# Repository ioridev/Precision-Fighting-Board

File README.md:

# [Precision-Fighting-Board](https://github.com/ioridev/Precision-Fighting-Board)

We all need to use this board in 20XX.  
[Discussions](https://github.com/ioridev/Precision-Fighting-Board/discussions)  
## Description

This project aims to develop the fastest game controller by utilizing the power of [Teensy 4.0](https://www.pjrc.com/store/teensy40.html). We strive to achieve a polling rate of 8000Hz, delivering unparalleled responsiveness for an immersive gaming experience.

## Where to Buy
  
Available for purchase on Booth. Buying from this shop directly supports the developers. For international customers, shipping outside of Japan is possible using address forwarding services like Buyee and Tenso.  

[https://iori-giken.booth.pm/](https://iori-giken.booth.pm/)

## Features

- High-speed USB communication using [Teensy 4.0](https://www.pjrc.com/store/teensy40.html)
- Targeting an impressive 8000Hz polling rate
- Precise and instantaneous input response
- X-input support
- No waiting time for debounce

## Installation
Open the PrecisionFightingBoard.TEENSY40.hex file in [Teensyduino 1.53](https://www.pjrc.com/teensy/td_158/TeensyduinoInstall.exe) and write to [Teensy 4.0](https://www.pjrc.com/store/teensy40.html).　
| Pin Number | Button      |
|------------|-------------|
| 0          | Up       |
| 1          | Down   |
| 2          | Left      |
| 3          | Right    |
| 4          | Home   |
| 5          | Back     |
| 6          | Start     |
| 7          | Y           |
| 8          | X           |
| 9          | RB         |
| 10         | LB         |
| 11         | A            |
| 12         | B            |
| 14         | RT         |
| 15         | LT          |
| 18         | L3          |
| 19         | R3          |

### Tips
Not good at soldering or making wires?  
Some models are equipped with pins from the beginning, so you can skip this complicated process by using this type of wire and wire for Brook.  
[Teensy 4.0 Pins](https://www.pjrc.com/store/teensy40_pins.html)

One GND with a pin is missing, so it must be branched with a breadboard or similar.　 

Or you can purchase Breakout Board on Amazon.  
  
[Breakout Board for Teensy 4.0](https://www.amazon.com/dp/B0C5SXFTC1?_encoding=UTF8&psc=1&ref_=cm_sw_r_cp_ud_dp_3P4ZTVVE18NE8B7TW8SG)

## Setting Up the Development Environment
Install Arduino IDE 1.8.13 and Teensyduino 1.53.

Clone this repository and copy the x-input/ArduinoXinput_Teensy/teensy directory to C:\Program Files (x86)\Arduino\hardware.

Open PrecisionFightingBoard.ino with the Arduino IDE, go to Tools, change the USB Type to XInput, and then upload it to the Teensy 4.0.

## Benchmark
### Polling rate test results 
I caught the continuous X-input button loop in my Python program and confirmed that it was around 0.125 ms.  
  
The program used for the test is in Precision-Fighting-Board/x-input/tester and anyone can try it out.

### Comparison with PicoBoard
tester/gamepad_response_time_comparison.py  
Gamepad 1 is a Precision-Fighting-Board.  
Gamepad 2 is a gp2040-ce  

### Comparison with Brook PS4+ Audio Fighting Board
Gamepad 1 is a Precision-Fighting-Board.  
Gamepad 2 is a Brook AFB  

### Use with WingmanFGC　
This is a test on a PC, but when used with WingmanFGC.  
Gamepad 1 is a Precision-Fighting-Board with WingmanFGC.  
Gamepad 2 is a gp2040-ce  
  
Good results with input lag of up to 5 ms.　　　

## Contributing

Contributions are welcome! If you'd like to contribute to this project, please follow these steps:

1. Fork the repository.
2. Create a new branch.
3. Make your enhancements or bug fixes.
4. Test thoroughly.
5. Submit a pull request detailing your changes.

## License

This project is licensed under the [MIT License](https://opensource.org/licenses/MIT). Please see the `LICENSE` file for more information.

## Acknowledgements

We would like to express our gratitude to the developers and contributors of Teency 4.0 for their amazing work and support.

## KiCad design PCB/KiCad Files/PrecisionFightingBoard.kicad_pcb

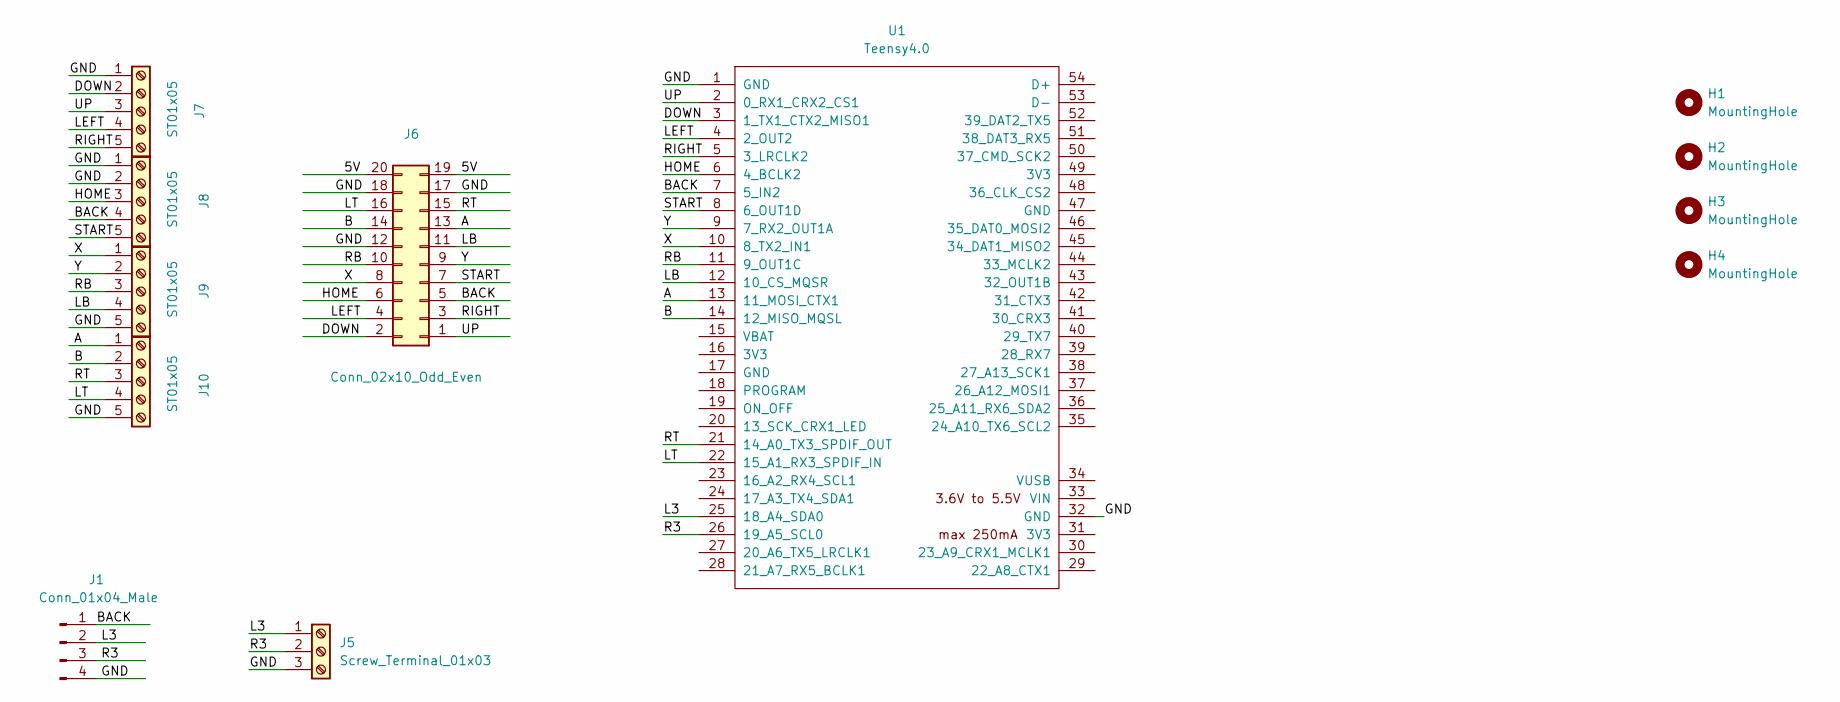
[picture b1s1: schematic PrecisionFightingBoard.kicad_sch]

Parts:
H1, H2, H3, H4: MountingHole; MountingHole_3.5mm
J1: Conn_01x04_Male; JST_PH_B4B-PH-K_1x04_P2.00mm_Vertical
J5: Screw_Terminal_01x03; TerminalBlock_MetzConnect_Type059_RT06303HBWC_1x03_P3.50mm_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
J6: Conn_02x10_Odd_Even; PinHeader_2x10_P2.54mm_Vertical
J7, J8, J9, J10: ST01x05; TerminalBlock_MetzConnect_Type059_RT06305HBWC_1x05_P3.50mm_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
U1: Teensy4.0; Teensy40

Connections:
/5V: J6.19, J6.20
/A: J6.13, J10.1, U1.13 (11_MOSI_CTX1)
/B: J6.14, J10.2, U1.14 (12_MISO_MQSL)
/BACK: J1.1, J6.5, J8.4, U1.7 (5_IN2)
/DOWN: J6.2, J7.2, U1.3 (1_TX1_CTX2_MISO1)
/GND: J1.4, J5.3, J6.12, J6.17, J6.18, J7.1, J8.1, J8.2, J9.5, J10.5, U1.1 (GND), U1.32 (GND)
/HOME: J6.6, J8.3, U1.6 (4_BCLK2)
/L3: J1.2, J5.1, U1.25 (18_A4_SDA0)
/LB: J6.11, J9.4, U1.12 (10_CS_MQSR)
/LEFT: J6.4, J7.4, U1.4 (2_OUT2)
/LT: J6.16, J10.4, U1.22 (15_A1_RX3_SPDIF_IN)
/R3: J1.3, J5.2, U1.26 (19_A5_SCL0)
/RB: J6.10, J9.3, U1.11 (9_OUT1C)
/RIGHT: J6.3, J7.5, U1.5 (3_LRCLK2)
/RT: J6.15, J10.3, U1.21 (14_A0_TX3_SPDIF_OUT)
/START: J6.7, J8.5, U1.8 (6_OUT1D)
/UP: J6.1, J7.3, U1.2 (0_RX1_CRX2_CS1)
/X: J6.8, J9.1, U1.10 (8_TX2_IN1)
/Y: J6.9, J9.2, U1.9 (7_RX2_OUT1A)

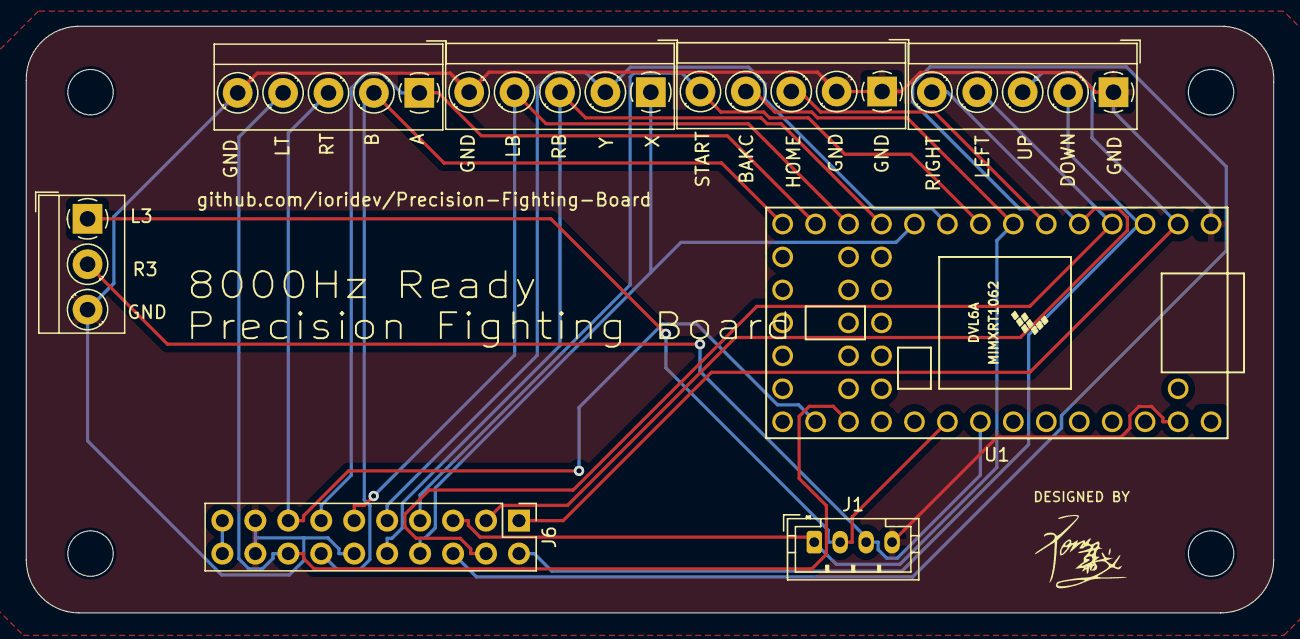
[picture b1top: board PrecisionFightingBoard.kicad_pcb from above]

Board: 2 copper layers, 96.1 x 45.2 mm, 12 parts (0 on the bottom side), 19 nets.

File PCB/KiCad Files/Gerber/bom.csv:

Designator,Footprint,Quantity,Value,LCSC Part #
"H1, H2, H3, H4",MountingHole_3.5mm,4,MountingHole,
J1,JST_PH_B4B-PH-K_1x04_P2.00mm_Vertical,1,Conn_01x04_Male,
"J10, J7, J8, J9",TerminalBlock_MetzConnect_Type059_RT06305HBWC_1x05_P3.50mm_Horizontal,4,ST01x05,
J5,TerminalBlock_MetzConnect_Type059_RT06303HBWC_1x03_P3.50mm_Horizontal,1,Screw_Terminal_01x03,
J6,PinHeader_2x10_P2.54mm_Vertical,1,Conn_02x10_Odd_Even,
U1,Teensy40,1,Teensy4.0,

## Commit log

2023-07-02 init
2023-07-02 add xinput
2023-07-02 add buttons
2023-07-02 rm: d-input
2023-07-02 add testar
2023-07-02 Create LICENSE
2023-07-02 fix d-input test program
2023-07-03 add d-input
2023-07-03 keyboard
2023-07-03 fix testar
2023-07-03 fix using pin
2023-07-03 add ArduinoXInput_Teensy
2023-07-03 rm teescy 3
2023-07-03 fix tester
2023-07-03 fix pin
2023-07-03 set xinput 8000Hz
2023-07-03 set 8000hz
2023-07-03 Make button pins easy to recognize.
2023-07-03 socd
2023-07-03 add license
2023-07-04 Update handle button bounce
2023-07-04 fix pit number
2023-07-04 add hex file
2023-07-04 Use eager debounce algorithm
2023-07-05 update hex file
2023-07-05 Improve debouncing in PrecisionFightingBoard.ino
2023-07-05 Refactor PrecisionFightingBoard.TEENSY40.hex for improved performance
2023-07-05 Improve debounce interval on PrecisionFightingBoard
2023-07-05 Refactor comments and improve explanation of debouncing behavior
2023-07-05 Optimize code for PrecisionFightingBoard.TEENSY40.hex file.
2023-07-05 Refactor button debouncing code for improved responsiveness.
2023-07-05 Improve precision in board's firmware.
2023-07-06 gamepad_response_time_comparison
2023-07-06 change debounce time 1 to 3
2023-07-10 add bounce lib
2023-07-10 activate the BOUNCE_LOCK_OUT debouncing method
2023-08-08 add xbox button
2023-08-08 update hex
2023-08-14 Revert "Merge pull request #16 from ioridev/add-homebutton"
    This reverts commit 0dd978a9f9cbb1a6a3a684d407d885486a9675fa, reversing
    changes made to 9f3a0dc22b2472b0e3af3778b5d182da007d6032.
2023-08-15 Revert "Revert "Merge pull request #16 from ioridev/add-homebutton""
    This reverts commit 1d300ed75660a2c9f941322a448a5569e7e30e9e.
2023-08-15 fix Dpad Right
2023-08-20 Remove unnecessary files and code for joystick and keyboard testing
2023-08-20 rm docs
2023-08-20 Update Pine posision
2023-08-20 gitignore
2023-08-20 git ignore
2023-08-20 add PCB
2023-08-20 rename
2023-08-20 add mounting hole
2023-08-20 Create a schematic
2023-08-20 add GND wire
2023-08-20 fix git ignore
2023-08-22 Remove limitation section from README.md file
2023-08-23 add connector
2023-08-23 Update button mappings in README file
2023-08-24 create PCB
2023-08-24 Wired
2023-08-25 add gerber files
2023-08-26 update pcb
2023-08-27 platformio
2023-08-29 Added rounded corners to the edges of the outline
2023-08-29 Changed 4-pin screw terminal to 3-pin.
2023-08-29 Updated wiring.
2023-08-29 add label
2023-08-29 update image
2023-09-01 mod maircpp
2023-09-07 fix pcb
2023-09-17 add gerber pos bom files
2024-02-21 fix: build error
2025-03-19 chore: update .gitignore to exclude .specstory files
2025-03-19 feat: add styleguide in Japanese
2025-03-19 chore: update .gitignore to exclude additional cursor rule files
2025-03-19 Add STM32H7 implementation with TinyUSB for Precision Fighting Board
2025-09-25 .vscode/extensions.json と platformio.ini を削除
2025-09-25 Add hall effect D-pad support
2025-09-26 D-padのピン設定にコメントを追加
2025-09-26 Calibrate hall d-pad thresholds from full stroke
2025-09-26 定数のコメントを追加し、可読性を向上させる
